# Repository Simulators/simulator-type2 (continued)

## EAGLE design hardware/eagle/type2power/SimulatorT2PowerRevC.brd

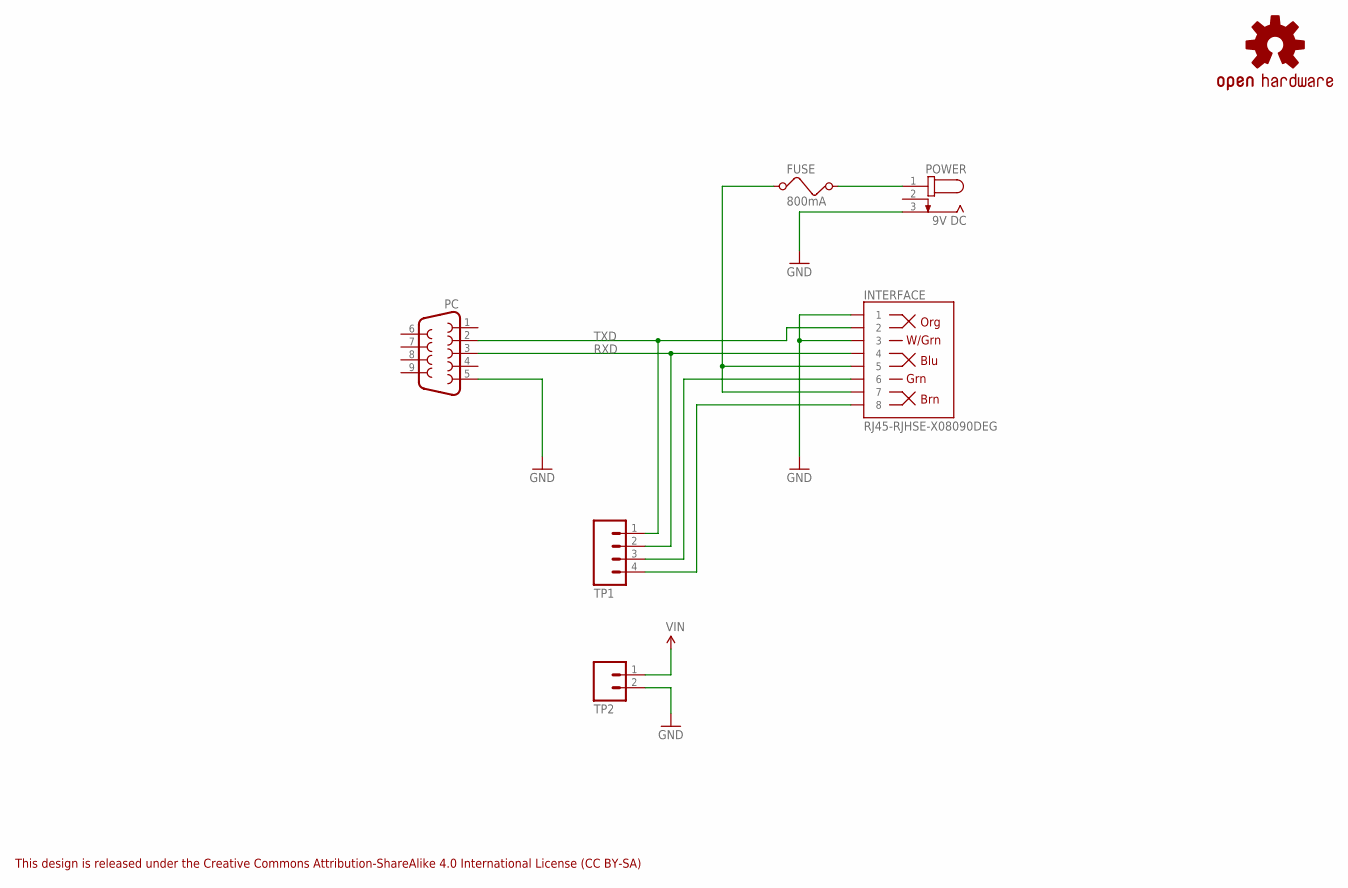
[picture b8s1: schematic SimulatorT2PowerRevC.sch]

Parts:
FUSE: 800mA; MCOMP-FUSE-HOLDER-PCB
INTERFACE: RJ45-RJHSE-X08090DEG; RJ45-RJHSE-5080
LOGO1: OSHW-LOGOS; OSHW-LOGO-S
PC: DB9-CONNECTOR-PCBFEMALE; MULTICOMP-DB9-FEMALE-PCB-90DEG
POWER: 9V DC; CLIFF-FC681465P-DC-JACK
TP1: M04PTH; 1X04
TP2: M02PTH; 1X02

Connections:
GND: INTERFACE.1, INTERFACE.3, PC.5, POWER.3, TP2.2
P8: INTERFACE.8, TP1.4
RXD: INTERFACE.4, PC.3, TP1.2
TX2: INTERFACE.6, TP1.3
TXD: INTERFACE.2, PC.2, TP1.1
VIN: FUSE.2, POWER.1, TP2.1
VIN2: FUSE.1, INTERFACE.5, INTERFACE.7

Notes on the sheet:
This design is released under the Creative Commons Attribution-ShareAlike 4.0 International License (CC BY-SA)

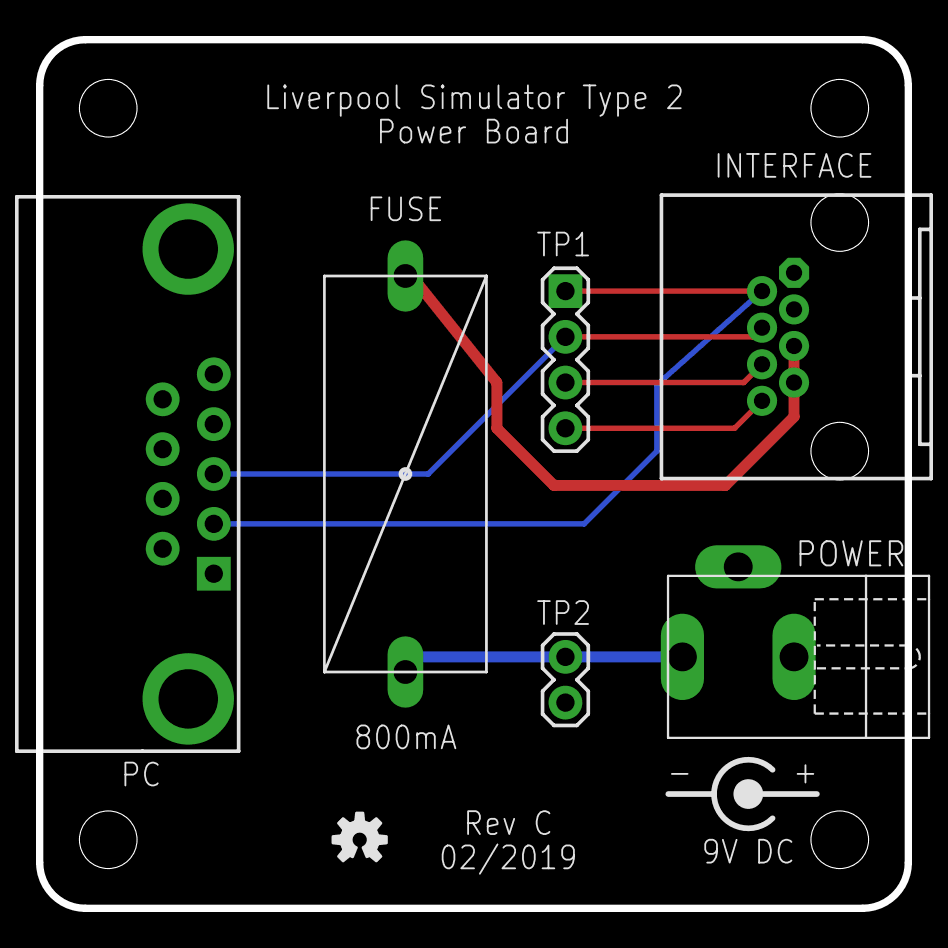
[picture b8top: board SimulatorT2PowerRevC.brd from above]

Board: 2 copper layers, 48.3 x 48.3 mm, 8 parts (0 on the bottom side), 7 nets.

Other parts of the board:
U$1: CENTRE-POS-SILK

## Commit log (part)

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2018-09-01 Upload firmware and PCB files
    Upload latest Type 2 firmware, Eagle and Gerber files into the new repo.
2018-09-01 docs/images
    Images from the documentation
2018-09-02 docs/images
    More images for documentation
2018-09-03 minor 3.2 firmware change
2018-09-07 Firmware 3.3
    CLI simplification, remove need to set numChannels by deriving it from
    enabledChannelMask.
2018-09-10 Build & Install Guide Draft v0.1
    First draft of the Type 2 Build & Installation Guide.
2018-09-10 Abel Configuration Guide Draft v0.1
    Draft v0.1 of the Abel Configuration Guide, and minor updates to the
    Build & Installation Guide.
2018-09-11 Minor fix to Interface board
2018-09-13 More draft guides
    New Beltower, Virtual Belfry, changed Abel
2018-09-17 Getting Started Guide Draft v0.1
2018-09-18 More OSH Park Gerbers
2018-10-28 Build Guide Update
    Minor corrections, PCB ordering, voltage regulator
2018-10-28 Fix Metadata
    Fix document metadata
2018-11-02 Part Code Change
    Changed the Farnell part code for the 1N4001 diode to a more available
    UK stocked item.
2018-11-02 Cost Estimation Tool
    Added an Excel cost estimation tool to give an estimate component cost
    based on the required number of interfaces and sesnsors.
2019-01-20 Interface Board Rev D
    Fixes a clearance problem with the alternative voltage regulator, and
    adds a second serial connection for future use. Enable layer 51 tDocu in
    Eagle to see alternate regulator outline. Closes #1
2019-01-24 Build Guide v.04
    Updated for Interface PCB Rev D, and added guidance on polarised
    components.
2019-01-25 Cost Estimation Tool v1.1
    Added the PSU
2019-02-05 Part changes
    Replace Amphenol 2-port RJ45 (no longer stocked by Farnell) with Amp TE
    Connectivity direct replacement. Remove link to Boardstuff programmer
    (no longer available) and replace with examples of hardware programmers.
    Update cost estimation tool.
2019-02-05 Updated custom Eagle library
2019-02-10 Documentation updates
    Diagram showing voltage test points, more GitHub links.
2019-02-17 Minor correction to build guide
    Correct error in the voltage checks pinout diagram.
2019-02-24 Eagle library update
    ZIF sockets, barrel connector polarity silkscreen label
2019-02-24 Power Board Rev C
    Add an indication of power supply polarity to the top silkscreen.
2019-04-18 Power Board RevC
2019-04-18 Second PC Board Rev A
    Enables support for a second PC by daisy-chaining the Second PC board
    between the Power Board and Interface. Requires Interface Rev D or
    later, or a mod to earlier Interface boards (described in the Eagle
    Description file).
2019-05-06 Board fixes
2019-05-12 2nd PC Board Doc Changes
    Update the Getting Started and Build & Installation Guides with support
    for the Second PC Board
2019-05-23 Old docs cleanup
2019-05-27 Interface RevE Boards
    Eagle files and Gerbers for Type 2 Interface Board Rev E
2019-05-27 Cost estimation tool update for Rev E
    Update the cost estimation tool for Rev E boards, clean up spurious
    images folder.
2019-05-27 Getting Started Guide v0.4
    Added link to ART Simulator Resources
2019-06-09 Rev E Build Guide
2019-06-20 Fuse Values
    Comment change only: Add note describing the fuses for resonators on Rev
    E boards,
2019-08-03 Enhanced surge protection
    Power Rev D, 2nd PC Rev B boards with improved surge protection,
    Gerbers, Cost Estimation tool, New enclosure drilling templates.
2019-08-03 Documentation updates
    All docs updated to v1.0. Updated Power Board to Rev D, Second PC to Rev
    B, both with improved surge protection. Remove OSH Park permalinks,
    Fixed dimension error on IR sensor enclosure. Add reference to enclosure
    drilling templates.
2019-09-29 Rev C Hardware
    Eagle, Gerbers, Library files for BAsic Serial Splitter Rev C
2019-10-01 Multi-PC Guide
    New Multi-PC Guide and resulting changes to other docs
2019-10-19 Fix bug in debounce code
    When misfiring, set the last observed value to the current state of the
    sensor in WAIT_FOR_DEBOUNCE, which is now HIGH again. If we don't do
    this, and the noise pulse is so close to the stable pulse that the
    stable pulse begins on the very next iteration of loop(), then the real
    pulse would be missed (because WAIT_FOR_INPUT is looking for a
    high-to-low transition). This has only been seen with a VERY noisy
2019-12-28 TRG 1.0
    Add TRG v1.0 (better late than never). Also silently fix reference Atmel
    -> Microchip in B&IG.
2020-01-02 TRG v1.1
    Added BAsic Serial Splitter details, more connector info, logic analyser
    trace to latency section.
2020-01-04 Doc update
    Add Virtual Striking Competition document.
2020-08-18 Documentation update
    Minor documentation update and upload of all documentation source
    material.
2021-07-22 Docs update
    Add information about faculty jurisdiction requirements, remove COVID-19
    references
2021-08-25 TRG update
    Added circuit protection features and DB9 connector pin-outs.
2021-08-27 Documentation update
    Drilling guides, DB9 part numbers, Serial pinouts
2022-05-18 Wider 5mm break-offs
    Issues with JLPCB rejecting panelised boards with 2.5mm stamp hole
    break-off tabs. Increased tab width to 5mm on all panelised boards.
2022-07-25 Firmware v3.6, Eagle Custom Library
    Improvements to Test Mode functionality and CLI. Also latest Eagle
    custom library which was missed previously.
2022-08-31 Board Housekeeping
    URL on silkscreens, caution messages, tidy up naming conventions.
2024-06-19 Firmware 3.7
    Interface firmware 3.7 adds support for MBI Protocol command 0xFD, to support the auto-configuration feature introduced in Abel 10.3.2. Documented in updated Abel configuration guide.
2024-06-19 Documentation Update
    Minor updates to all guides, mainly fixing external links.
2024-06-19 Documentation Sources
    Updated documentation source files and screenshots.
2024-06-20 Documentation updates
    Minor updates to guides, fixing external links, updating to later versions of apps..
2024-06-27 Documentation updates
    Check and updated all part numbers, some minor component changes.
2024-06-27 Documentation sources
    Sources for latest documentation updates.
2024-06-27 Cost Estimation Tool Update
    Update Cost Estimation Tool with latest (June 2024) costs, and add support for costing the Multi-PC options (Second PC Board, Basic Serial Splitter).
2024-08-28 Multi-PC Documentation Improvements
    Update diagrams to show cable types more clearly, add a table of possible module combinations for multi-PC configurations.
2025-01-27 Update index pages
2025-01-28 Update index
2025-02-21 T1-T2 Adapter Resources
    Eagle files, Gerbers, diagrams & images for the Type 1 - Type 2 Adapter board.
2025-03-03 T1-T2 Interface Adapter Documentation
    Updated the Technical Reference Guide with details of the T1-T2 Interface Adapter
2025-04-14 Updated Release Notes
2025-04-22 KiCad structure
    Preparatory work for KiCad migration.
2025-04-24 Kicad Gerbers
    Non-panelised Gerbers for all boards excluding the MR sensor.
2025-04-24 Kicad Projects
    Kicad archived Projects for all boards excluding the MR sensor.
2025-04-24 Kicad Panel Gerbers
    Panelised Gerbers for sensor/power/2nd PC excluding the MR sensor.
2025-04-24 A1120 MR Sensor
    Adds support for the Allegro Microsystems A1120 Hall Effect sensor in addition to the Honeywell 2SS52M Magneto-Resistive sensor. Documentation to follow.
2025-05-07 KiCad Documentation
    Updated documentation set with schematics and board layouts generated by KiCad (except for the MR Sensor).
2025-05-07 A1120 Documentation
    Documentation updates for A1120 support.
2025-05-07 Fix Typo
2025-05-07 Tidy up merge
2025-05-09 Cost Estimation Tool v1.6
    Cost estimation tool updated to support option of A110EUA-T Hall Effect sensors, and change supplier of 2SS52M MR device to RS (no longer stocked by Farnell).
2025-05-19 Update index.html
    Cost Estimation Tool v1.6 documentation link.
2025-05-19 Update README.md
    Eagle -> KiCad
2025-06-23 Firmware 3.8
    Add swing delta timing as an additional debug option. Change debug message format to have identifying letter first.
2025-07-01 Beltower 14.05
    Noted as tested against Beltower 14.05
2025-07-07 Firmware 3.8
    Added time delta between pulses to debug pulse timer output.
2025-07-09 A1120 Support
    Completion of A1120 Hall Effect sensor support. Add recommended attribution details to all guides.
2025-07-09 Firmware 3.8
2025-07-09 Post-Merge Cleanup
2025-07-18 Add Magnet Positioning Guide
    Add printable guide to assist with aligning magnets and sensors.
2026-03-23 Update KiCad_Libraries.zip
    Add LRSP logo symbols with PCB silkscreen and copper footprint versions.
